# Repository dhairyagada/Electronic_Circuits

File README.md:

# Electronic_Circuits
Various Basic Electronic Circuits

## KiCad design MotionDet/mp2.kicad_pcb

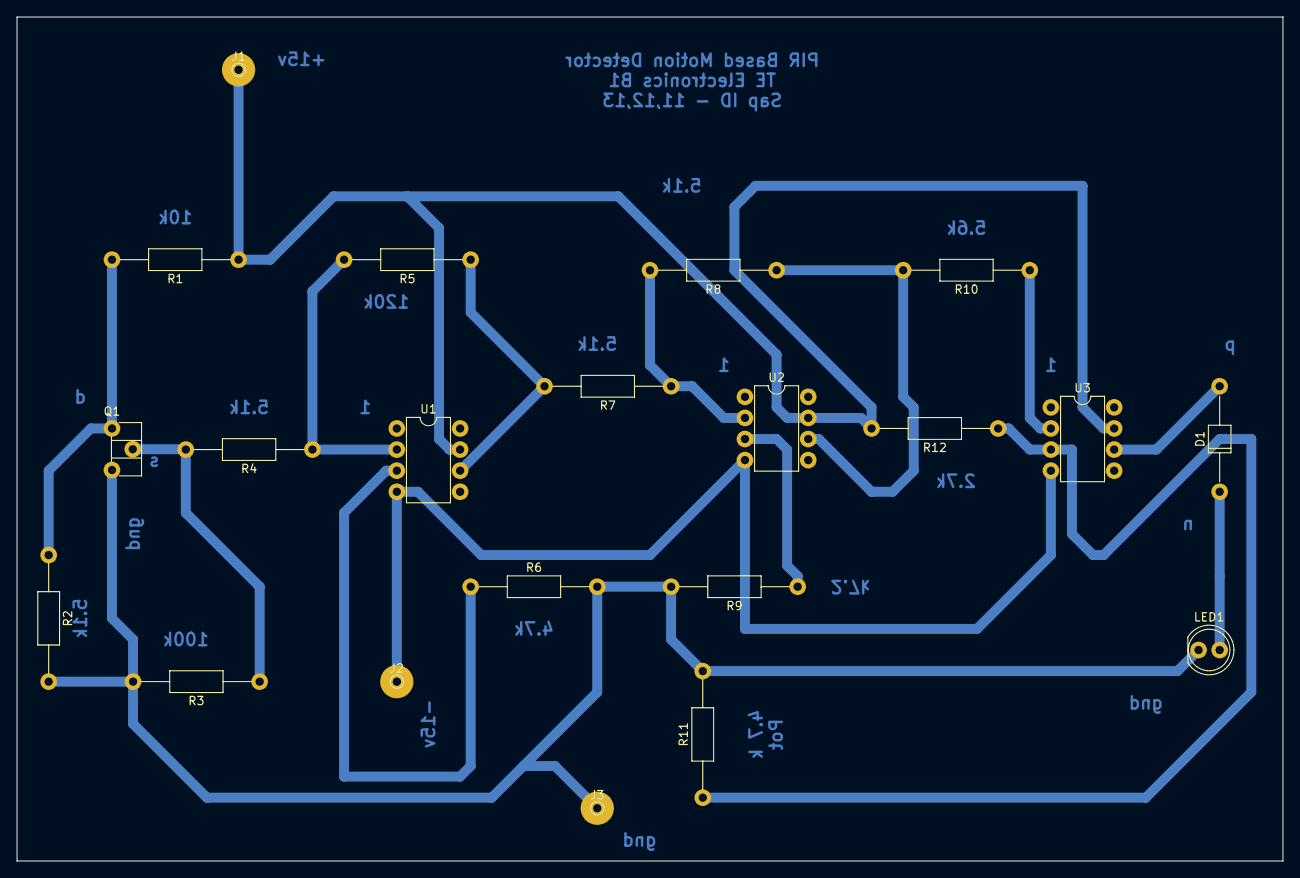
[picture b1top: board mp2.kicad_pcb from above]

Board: 2 copper layers, 152.4 x 101.6 mm, 21 parts (0 on the bottom side), 15 nets.

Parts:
D1: D; D_T-1_P12.70mm_Horizontal
J1: +Vcc; PINTST
J2: -Vcc; PINTST
J3: Ground; PINTST
LED1: LED; LED_D5.0mm
Q1: Q_NMOS_DSG; Potentiometer_Trimmer_ACP_CA6h_Vertical
R1: 10K; R_Axial_DIN0207_L6.3mm_D2.5mm_P15.24mm_Horizontal
R2, R4, R7, R8: 5.1K; R_Axial_DIN0207_L6.3mm_D2.5mm_P15.24mm_Horizontal
R3: 100K; R_Axial_DIN0207_L6.3mm_D2.5mm_P15.24mm_Horizontal
R5: 120K; R_Axial_DIN0207_L6.3mm_D2.5mm_P15.24mm_Horizontal
R6: 4.7K; R_Axial_DIN0207_L6.3mm_D2.5mm_P15.24mm_Horizontal
R9, R12: 2.7K; R_Axial_DIN0207_L6.3mm_D2.5mm_P15.24mm_Horizontal
R10: 5.6K; R_Axial_DIN0207_L6.3mm_D2.5mm_P15.24mm_Horizontal
R11: 4.7 K; R_Axial_DIN0207_L6.3mm_D2.5mm_P15.24mm_Horizontal
U1, U2, U3: LM741; DIP-8_W7.62mm

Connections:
/Vc: J1.1, R1.1, R12.2, U1.7, U2.7, U3.7
/Ve: J2.1, U1.4, U2.4, U3.4
GND: J3.1, LED1.1, Q1.3, R2.2, R3.2, R6.2, R9.2, R11.2
unnamed: D1.1, LED1.2
unnamed: D1.2, U3.6
unnamed: Q1.1, R1.2, R2.1
unnamed: Q1.2, R3.1, R4.2
unnamed: R4.1, R5.2, U1.2
unnamed: R5.1, R7.2, U1.6
unnamed: R6.1, U1.3
unnamed: R7.1, R8.2, U2.2
unnamed: R9.1, U2.3
unnamed: R10.1, U3.2
unnamed: R8.1, R10.2, U2.6
unnamed: R11.1, R12.1, U3.3

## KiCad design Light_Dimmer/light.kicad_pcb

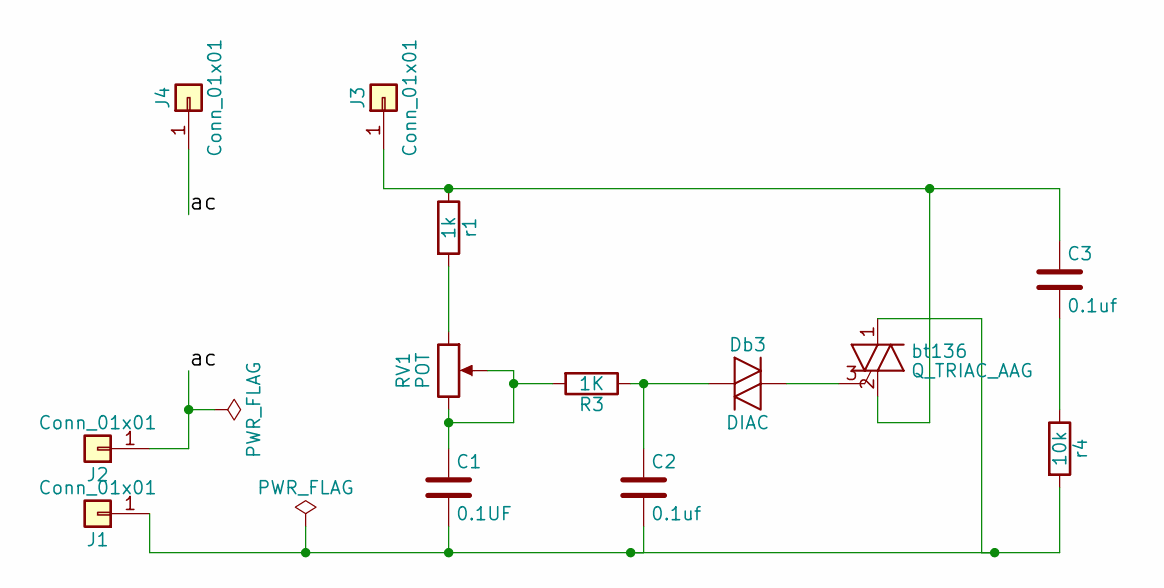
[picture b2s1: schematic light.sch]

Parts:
C1: 0.1UF; C_Rect_L16.5mm_W4.7mm_P15.00mm_MKT
C2, C3: 0.1uf; C_Rect_L16.5mm_W4.7mm_P15.00mm_MKT
Db3: DIAC; D_DO-41_SOD81_P10.16mm_Horizontal
J1, J2, J3, J4: Conn_01x01; Banana_Jack_1Pin
R3: 1K; R_Axial_DIN0414_L11.9mm_D4.5mm_P15.24mm_Horizontal
RV1: POT; Potentiometer_Alps_RK09K_Horizontal
bt136: Q_TRIAC_AAG; IRReceiver_Vishay_MINICAST-3pin
r1: 1k; R_Axial_DIN0414_L11.9mm_D4.5mm_P15.24mm_Horizontal
r4: 10k; R_Axial_DIN0414_L11.9mm_D4.5mm_P15.24mm_Horizontal

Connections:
/ac: J2.1, J4.1
unnamed: C1.1, R3.2, RV1.2, RV1.3
unnamed: C1.2, C2.2, J1.1, bt136.1 (A1), r4.2
unnamed: C2.1, Db3.1 (K), R3.1
unnamed: C3.1, J3.1, bt136.2 (A2), r1.1
unnamed: C3.2, r4.1
unnamed: Db3.2 (A), bt136.3 (G)
unnamed: RV1.1, r1.2

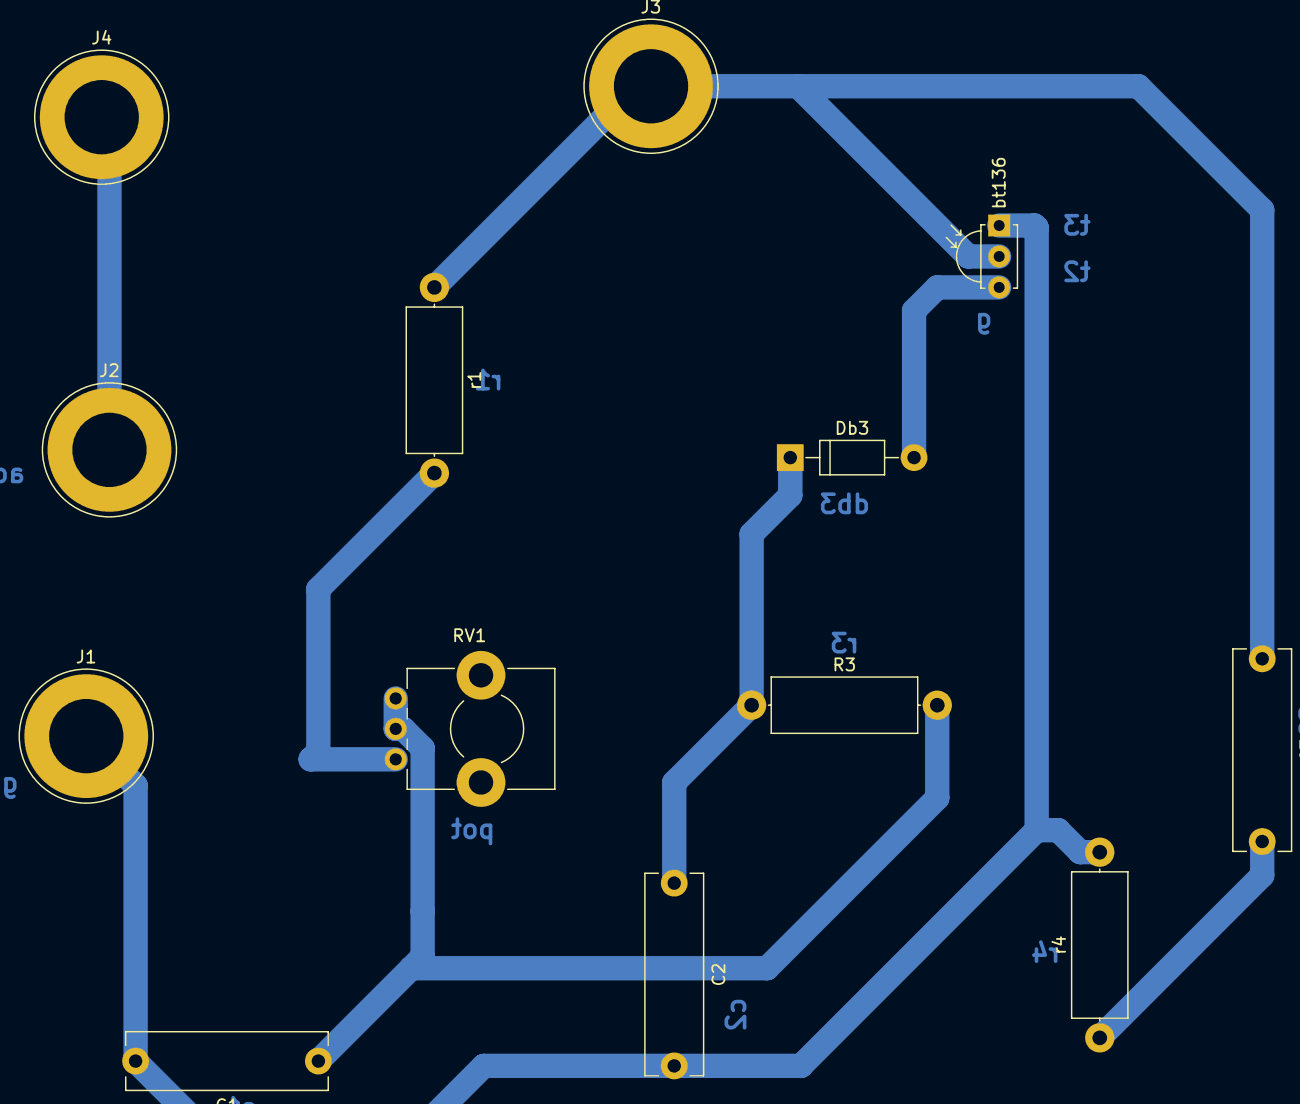
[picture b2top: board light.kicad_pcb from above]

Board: 2 copper layers, 13 parts (0 on the bottom side), 8 nets.

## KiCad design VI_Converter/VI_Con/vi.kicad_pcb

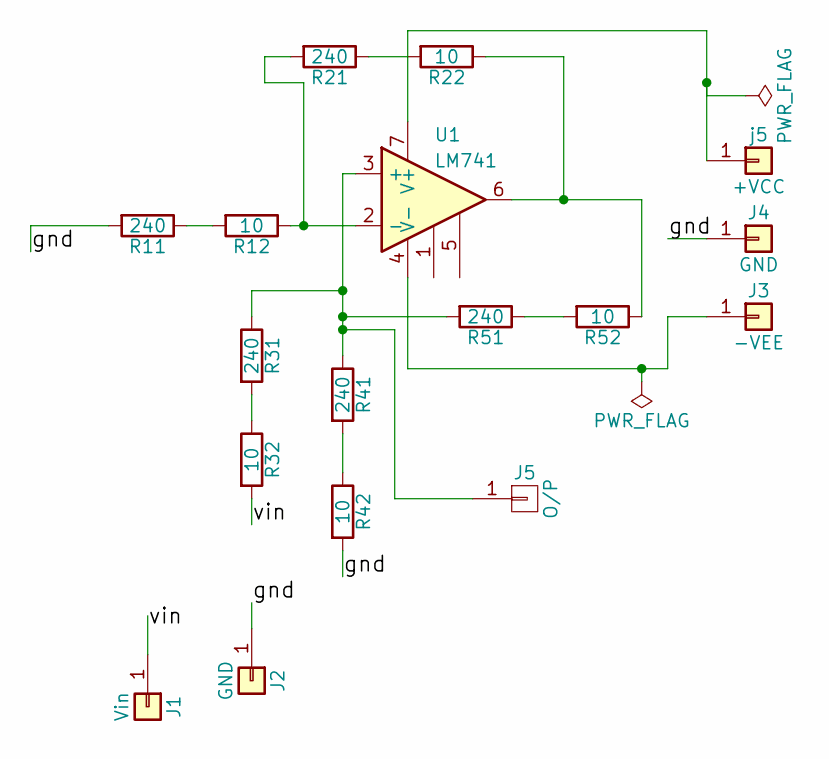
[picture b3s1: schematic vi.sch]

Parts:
J1: Vin; Banana_Jack_1Pin
J2, J4: GND; Banana_Jack_1Pin
J3: -VEE; Banana_Jack_1Pin
J5: O/P; Banana_Jack_1Pin
R11, R21, R31, R41, R51: 240; R_Axial_DIN0207_L6.3mm_D2.5mm_P15.24mm_Horizontal
R12, R22, R32, R42, R52: 10; R_Axial_DIN0207_L6.3mm_D2.5mm_P15.24mm_Horizontal
U1: LM741; DIP-8_W7.62mm
j5: +VCC; Banana_Jack_1Pin

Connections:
/gnd: J2.1, J4.1, R11.2, R42.2
/vin: J1.1, R32.2
unnamed: J3.1, U1.4 (V-)
unnamed: J5.1, R31.1, R41.1, R51.2, U1.3 (+)
unnamed: R11.1, R12.2
unnamed: R12.1, R21.2, U1.2 (-)
unnamed: R21.1, R22.2
unnamed: R22.1, R52.1, U1.6
unnamed: R31.2, R32.1
unnamed: R41.2, R42.1
unnamed: R51.1, R52.2
unnamed: U1.7 (V+), j5.1

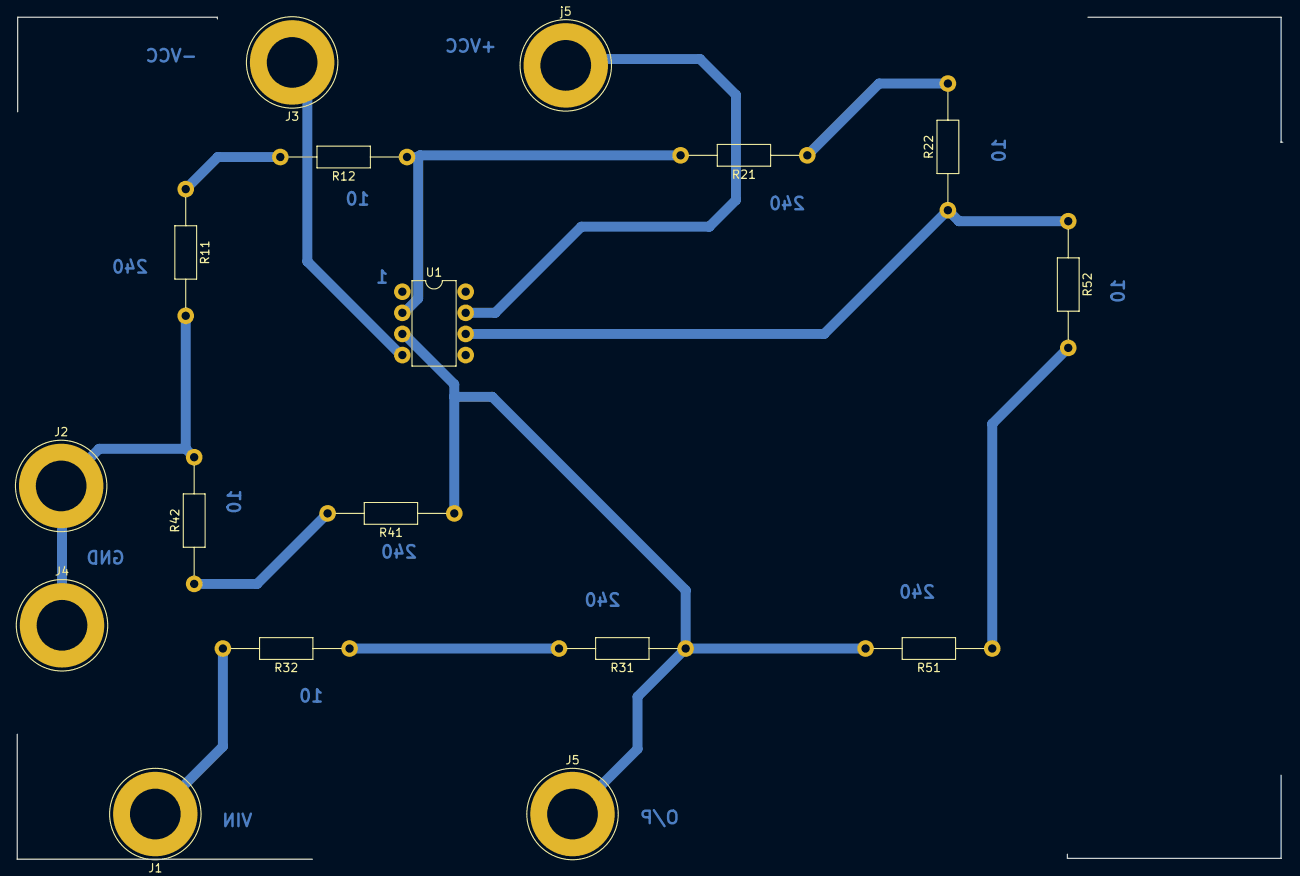
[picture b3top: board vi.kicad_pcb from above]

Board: 2 copper layers, 152.2 x 101.3 mm, 17 parts (0 on the bottom side), 12 nets.

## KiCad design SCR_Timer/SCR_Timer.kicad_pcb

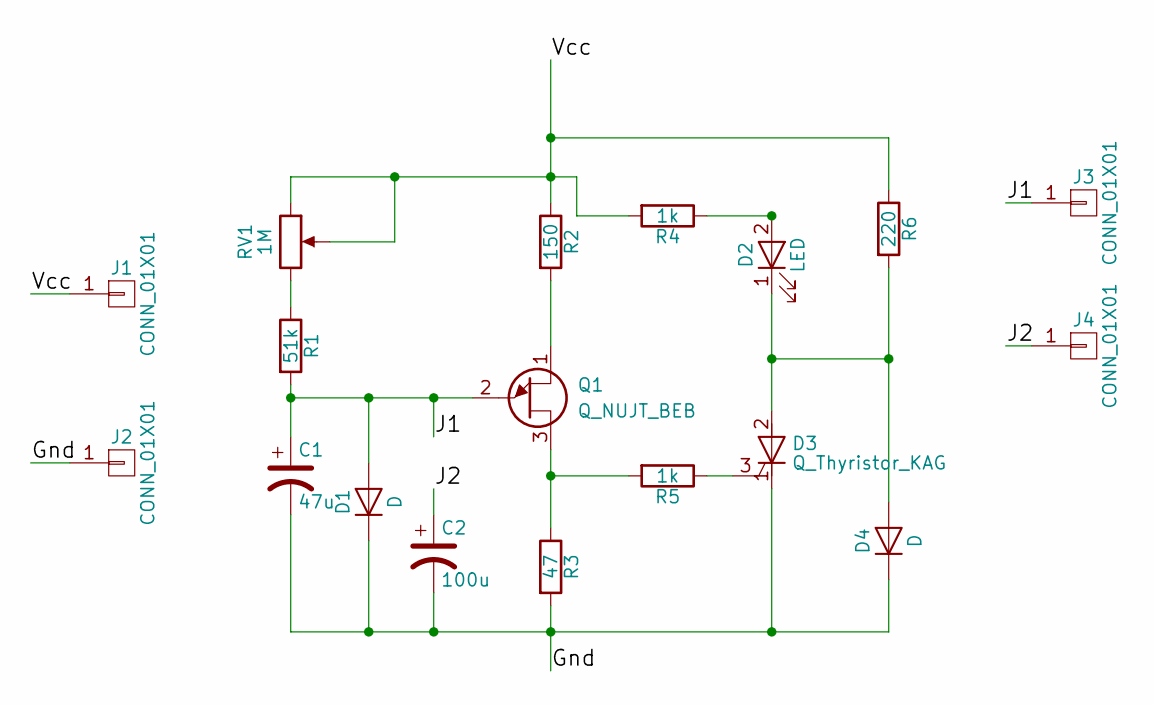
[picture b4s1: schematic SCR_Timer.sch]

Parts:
C1: 47u; CP_Radial_D12.5mm_P7.50mm
C2: 100u; CP_Radial_D18.0mm_P7.50mm
D1, D4: D; R_Axial_DIN0207_L6.3mm_D2.5mm_P5.08mm_Vertical
D2: LED; LED_D5.0mm
D3: Q_Thyristor_KAG; IRReceiver_Vishay_MINICAST-3pin
J1, J2, J3, J4: CONN_01X01; Banana_Jack_1Pin
Q1: Q_NUJT_BEB; Potentiometer_Trimmer_ACP_CA14h5_Vertical_Px5.0mm_Py10.0mm
R1: 51k; R_Axial_DIN0309_L9.0mm_D3.2mm_P20.32mm_Horizontal
R2: 150; R_Axial_DIN0309_L9.0mm_D3.2mm_P20.32mm_Horizontal
R3: 47; R_Axial_DIN0309_L9.0mm_D3.2mm_P20.32mm_Horizontal
R4, R5: 1k; R_Axial_DIN0309_L9.0mm_D3.2mm_P20.32mm_Horizontal
R6: 220; R_Axial_DIN0309_L9.0mm_D3.2mm_P20.32mm_Horizontal
RV1: 1M; Potentiometer_VishaySpectrol_248GJ_249GJ_Horizontal

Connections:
/Gnd: C1.2, C2.2, D1.1 (K), D3.1 (K), D4.1 (K), J2.1, R3.2
/J1: C1.1, D1.2 (A), J3.1, Q1.2 (E), R1.2
/J2: C2.1, J4.1
/Vcc: J1.1, R2.1, R4.2, R6.1, RV1.1, RV1.2
unnamed: D2.1 (K), D3.2 (A), D4.2 (A), R6.2
unnamed: D2.2 (A), R4.1
unnamed: D3.3 (G), R5.1
unnamed: Q1.1 (B2), R2.2
unnamed: Q1.3 (B1), R3.1, R5.2
unnamed: R1.1, RV1.3

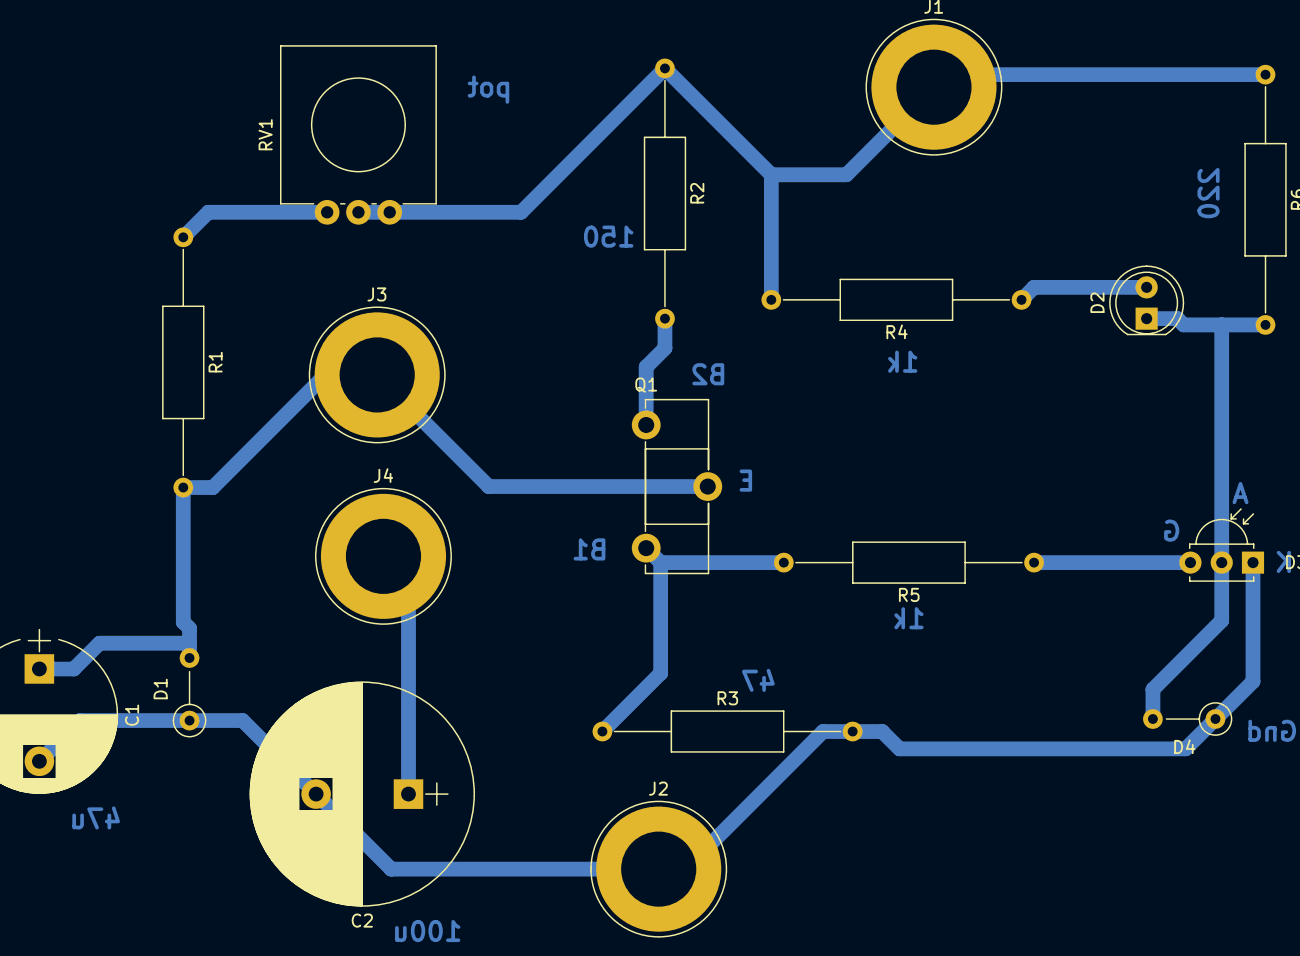
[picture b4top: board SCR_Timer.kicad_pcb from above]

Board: 2 copper layers, 18 parts (0 on the bottom side), 10 nets.

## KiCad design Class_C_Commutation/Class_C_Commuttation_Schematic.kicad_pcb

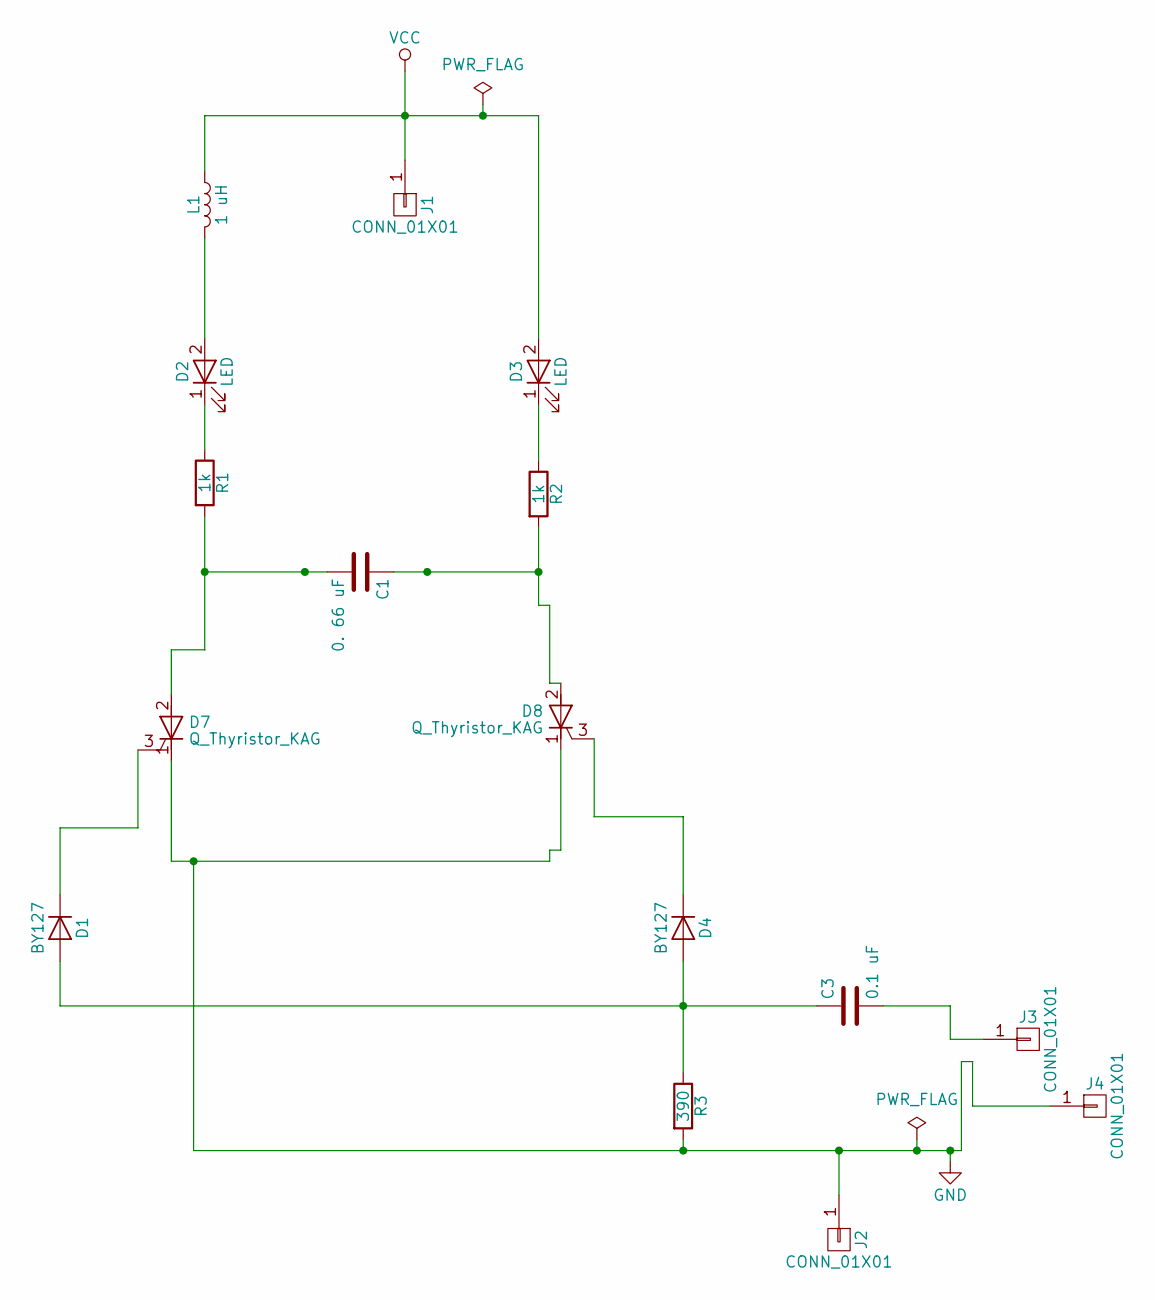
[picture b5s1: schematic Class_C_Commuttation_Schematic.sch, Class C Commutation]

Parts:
C1: 0. 66 uF; C_Axial_L22.0mm_D9.5mm_P27.50mm_Horizontal
C3: 0.1 uF; C_Disc_D3.0mm_W2.0mm_P2.50mm
D1, D4: BY127; R_Axial_DIN0516_L15.5mm_D5.0mm_P30.48mm_Horizontal
D2, D3: LED; LED_D5.0mm
D7, D8: Q_Thyristor_KAG; IRReceiver_Vishay_MINICAST-3pin
J1, J2, J3, J4: CONN_01X01; Banana_Jack_1Pin
L1: 1 uH; R_Axial_DIN0207_L6.3mm_D2.5mm_P15.24mm_Horizontal
R1, R2: 1k; R_Axial_DIN0516_L15.5mm_D5.0mm_P30.48mm_Horizontal
R3: 390; R_Axial_DIN0207_L6.3mm_D2.5mm_P15.24mm_Horizontal

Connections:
GND: D7.1 (K), D8.1 (K), J2.1, J4.1, R3.2
unnamed: C1.1, D8.2 (A), R2.2
unnamed: C1.2, D7.2 (A), R1.2
unnamed: C3.1, D1.2 (A), D4.2 (A), R3.1
unnamed: C3.2, J3.1
unnamed: D1.1 (K), D7.3 (G)
unnamed: D2.1 (K), R1.1
unnamed: D2.2 (A), L1.2
unnamed: D3.1 (K), R2.1
unnamed: D4.1 (K), D8.3 (G)
VCC: D3.2 (A), J1.1, L1.1

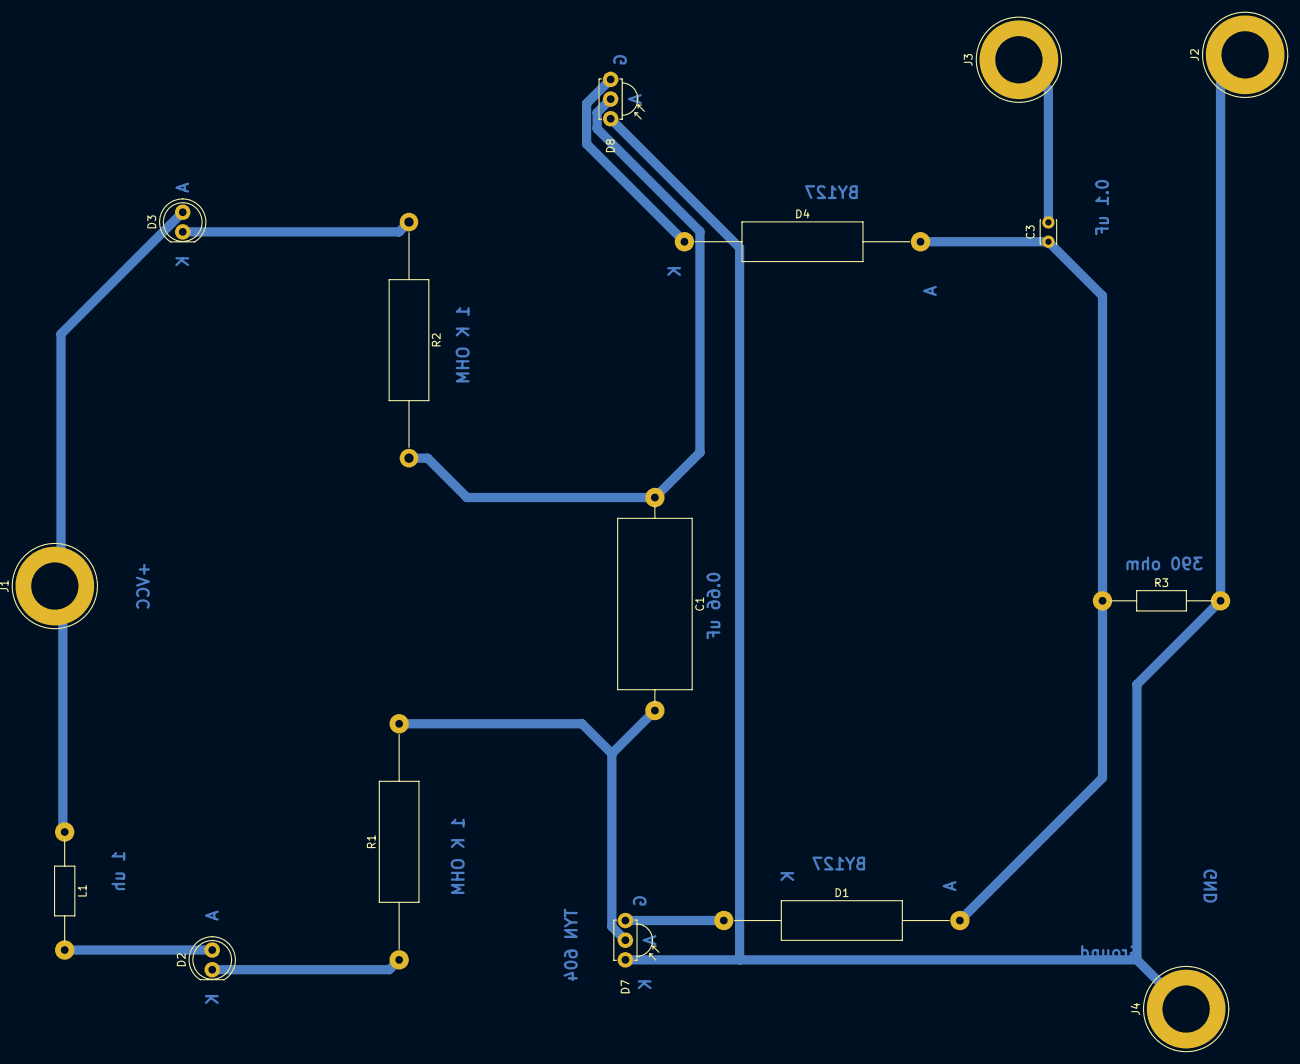
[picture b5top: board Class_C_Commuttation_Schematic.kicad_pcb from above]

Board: 2 copper layers, 16 parts (0 on the bottom side), 11 nets.

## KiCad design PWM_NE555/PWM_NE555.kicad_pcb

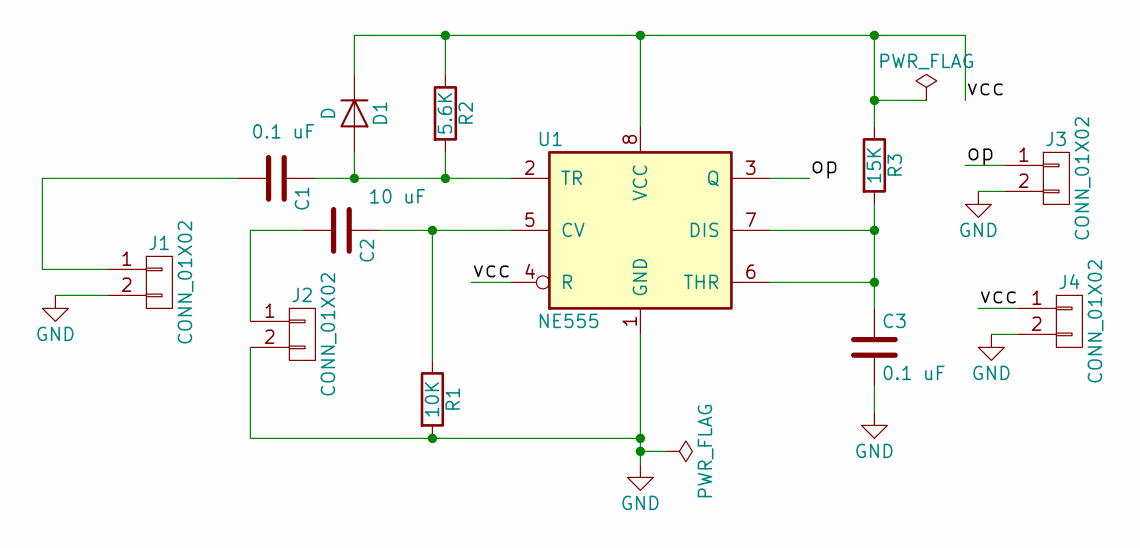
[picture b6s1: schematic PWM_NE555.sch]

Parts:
C1, C3: 0.1 uF; C_Disc_D3.0mm_W2.0mm_P2.50mm
C2: 10 uF; C_Disc_D3.0mm_W2.0mm_P2.50mm
D1: D; D_DO-201AD_P15.24mm_Horizontal
J1, J2, J3, J4: CONN_01X02; TerminalBlock_Pheonix_MKDS1.5-2pol
R1: 10K; R_Axial_DIN0207_L6.3mm_D2.5mm_P15.24mm_Horizontal
R2: 5.6K; R_Axial_DIN0207_L6.3mm_D2.5mm_P15.24mm_Horizontal
R3: 15K; R_Axial_DIN0207_L6.3mm_D2.5mm_P15.24mm_Horizontal
U1: NE555; DIP-8_W7.62mm

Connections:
/op: J3.1, U1.3 (Q)
/vcc: D1.1 (K), J4.1, R2.1, R3.1, U1.4 (R), U1.8 (VCC)
GND: C3.2, J1.2, J2.2, J3.2, J4.2, R1.2, U1.1 (GND)
unnamed: C1.1, D1.2 (A), R2.2, U1.2 (TR)
unnamed: C1.2, J1.1
unnamed: C2.1, R1.1, U1.5 (CV)
unnamed: C2.2, J2.1
unnamed: C3.1, R3.2, U1.6 (THR), U1.7 (DIS)

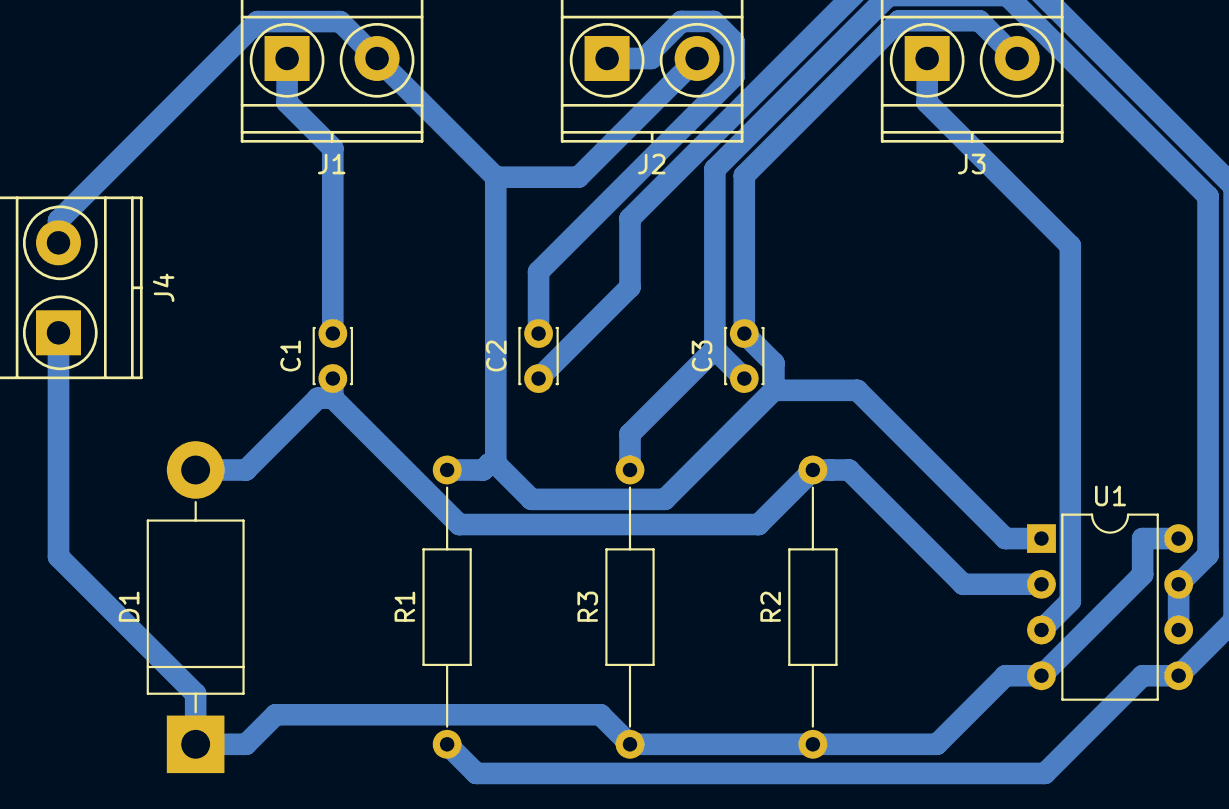
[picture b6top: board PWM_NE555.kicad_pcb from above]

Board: 2 copper layers, 12 parts (0 on the bottom side), 8 nets.

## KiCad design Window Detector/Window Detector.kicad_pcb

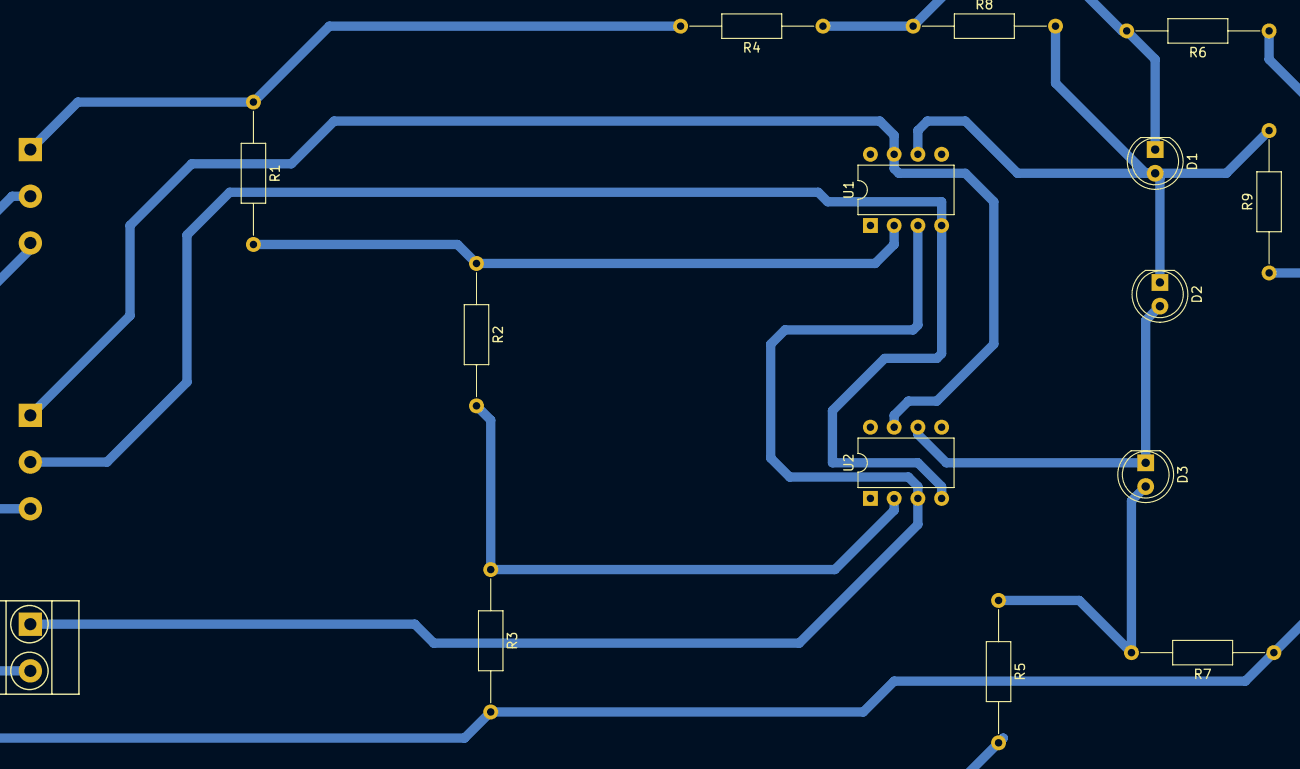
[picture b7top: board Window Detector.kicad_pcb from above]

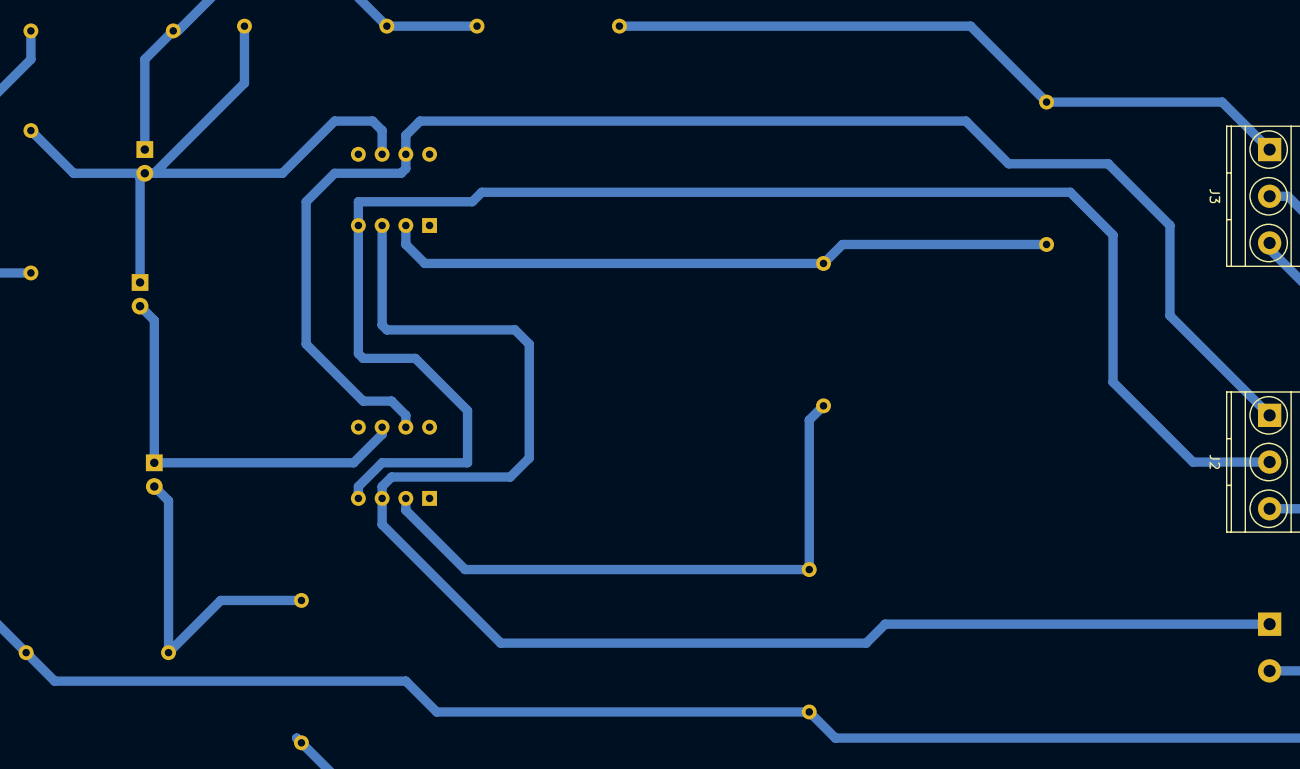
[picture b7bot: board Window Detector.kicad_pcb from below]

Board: 2 copper layers, 17 parts (2 on the bottom side), 12 nets.

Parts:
D1, D2, D3: LED; LED_D5.0mm
J1: CONN_01X02; TerminalBlock_Pheonix_MKDS1.5-2pol
J2, J3: CONN_01X03; TerminalBlock_Pheonix_MKDS1.5-3pol
R1, R2, R3, R8: 10K; R_Axial_DIN0207_L6.3mm_D2.5mm_P15.24mm_Horizontal
R4, R5: 4.7K; R_Axial_DIN0207_L6.3mm_D2.5mm_P15.24mm_Horizontal
R6, R7: 5.6K; R_Axial_DIN0207_L6.3mm_D2.5mm_P15.24mm_Horizontal
R9: 6.2K; R_Axial_DIN0207_L6.3mm_D2.5mm_P15.24mm_Horizontal
U1, U2: LM741; DIP-8_W7.62mm

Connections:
+9V: J3.1, R1.1, R4.2
+15V: J2.1, U1.7, U2.7
-9VA: J3.2, R5.2
-15V: J2.2, U1.4, U2.4
/Vin: J1.1, U1.3, U2.3
GND: J1.2, J2.3, J3.3, R3.2, R6.1, R7.1, R9.1
unnamed: D1.1, R4.1, R6.2, R8.1
unnamed: D1.2, D2.1, R8.2, R9.2, U1.6
unnamed: D2.2, D3.1, U2.6
unnamed: D3.2, R5.1, R7.2
unnamed: R1.2, R2.1, U1.2
unnamed: R2.2, R3.1, U2.2

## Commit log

2017-09-28 Window Detector
2017-10-03 Gitignore file
2017-10-03 Made some changes in circuit
    Yet to update the changes in the pcb design
2017-10-05 Initialized PWM using 555 Project
2017-10-05 Added Files for PWM_NE555
2017-10-06 Made NE555 PWM schematic
2017-10-06 Added Footprints to the Schematic Components
2017-10-06 Made PwM NE555 PCB Layout and Tracks
2017-10-14 Class C Commutation
2017-10-14 Class C commutation corrected pcb layout
2017-10-15 Added SCR Timer Schematic and assosciated footprints
2017-10-15 SCR Timer PCB Layout
2017-10-15 V to I converter LT Spice Schematic
2017-10-15 Schmitt Trigger using ne555 schematic
2017-10-15 Removed wrong schematic of Window detector
2017-10-15 Added Schmitt Trigger Using NE555 PCB Layout
2017-10-17 Added V to I Converter
2017-10-20 Added Light Dimmer Schematic and PCB layout KiCad files
2017-10-27 Motion Detector Schematic
2017-10-27 Motion Detector PCB Layout Tracks
2017-10-27 PCB Layout Finalized
